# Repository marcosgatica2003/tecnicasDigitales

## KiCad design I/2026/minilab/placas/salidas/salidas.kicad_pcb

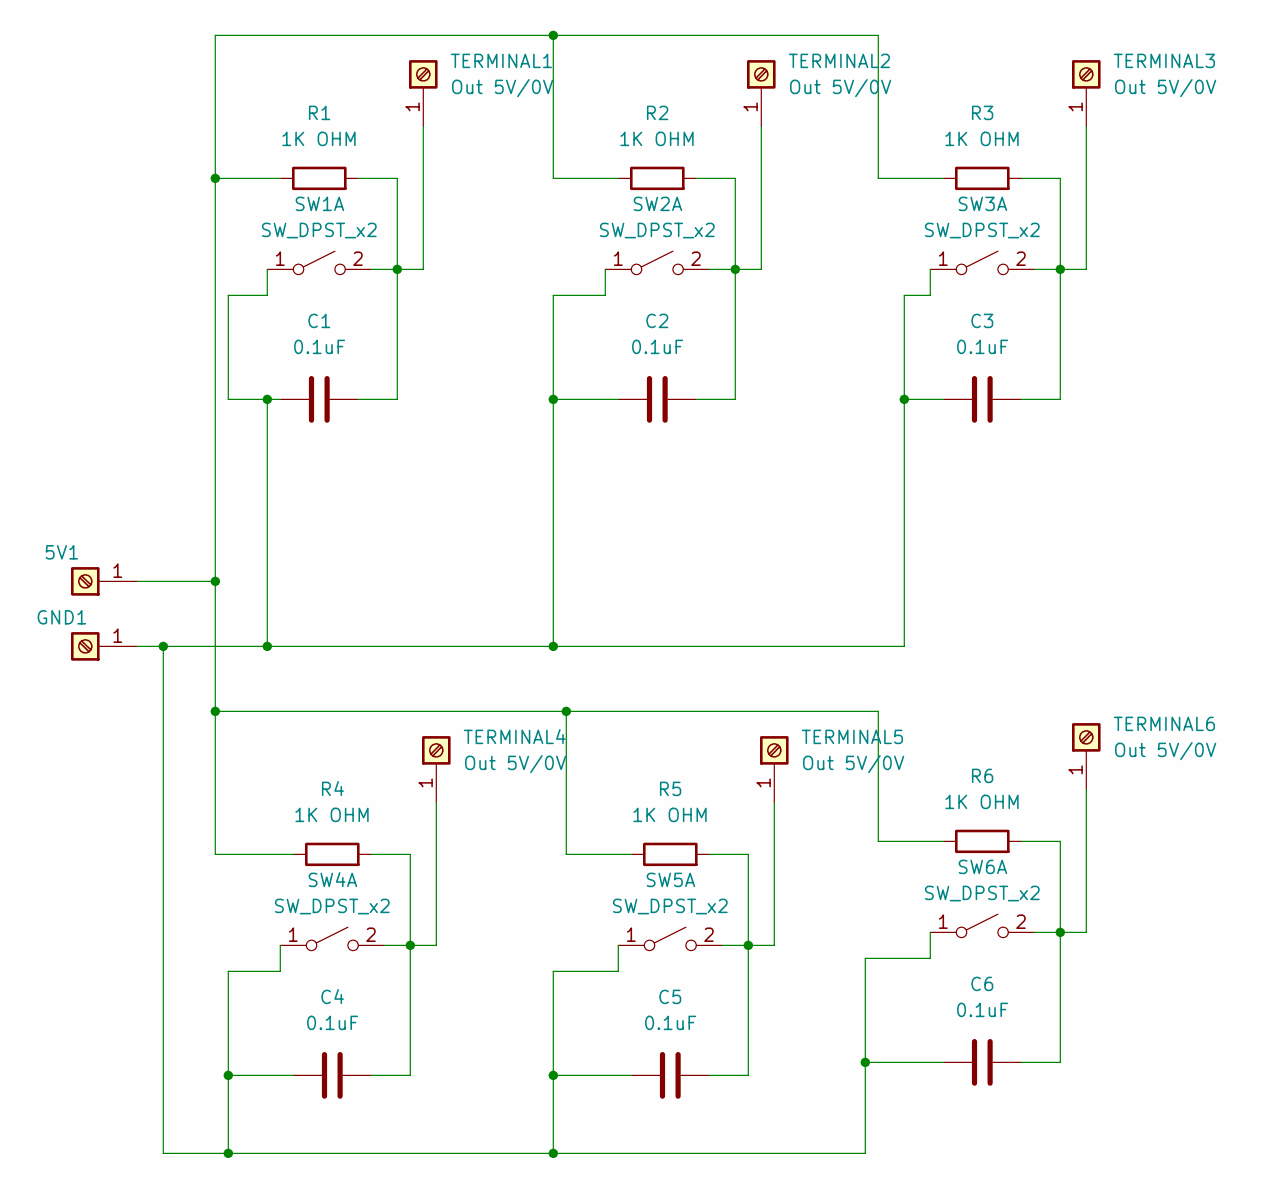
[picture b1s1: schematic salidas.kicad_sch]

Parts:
5V1: PinHeader_1x01_P1.00mm_Vertical
C1, C2, C3, C4, C5, C6: 0.1uF; CP_Radial_D5.0mm_P2.00mm
GND1: PinHeader_1x01_P1.00mm_Vertical
R1, R2, R3, R4, R5, R6: 1K OHM; R_Axial_DIN0207_L6.3mm_D2.5mm_P7.62mm_Horizontal
SW1, SW2, SW3, SW4, SW5, SW6: SW_DPST_x2; SW_DIP_SPSTx01_Slide_9.78x4.72mm_W7.62mm_P2.54mm
TERMINAL1, TERMINAL2, TERMINAL3, TERMINAL4, TERMINAL5, TERMINAL6: Out 5V/0V; PinHeader_1x01_P1.00mm_Vertical

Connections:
unnamed: 5V1.1 (Pin_1_1), R1.1, R2.1, R3.1, R4.1, R5.1, R6.1
unnamed: C1.1, C2.1, C3.1, C4.1, C5.1, C6.1, GND1.1 (Pin_1_1), SW1.1 (A), SW2.1 (A), SW3.1 (A), SW4.1 (A), SW5.1 (A), SW6.1 (A)
unnamed: C1.2, R1.2, SW1.2 (B), TERMINAL1.1 (Pin_1_1)
unnamed: C2.2, R2.2, SW2.2 (B), TERMINAL2.1 (Pin_1_1)
unnamed: C3.2, R3.2, SW3.2 (B), TERMINAL3.1 (Pin_1_1)
unnamed: C4.2, R4.2, SW4.2 (B), TERMINAL4.1 (Pin_1_1)
unnamed: C5.2, R5.2, SW5.2 (B), TERMINAL5.1 (Pin_1_1)
unnamed: C6.2, R6.2, SW6.2 (B), TERMINAL6.1 (Pin_1_1)

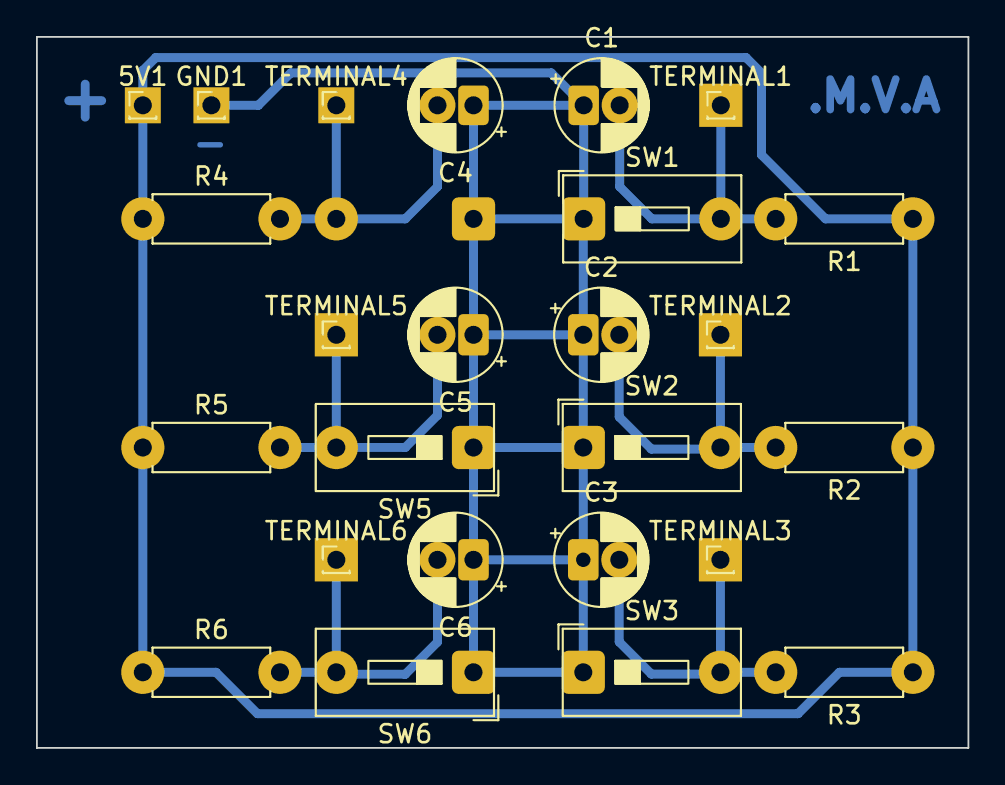
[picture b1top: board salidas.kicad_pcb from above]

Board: 2 copper layers, 51.8 x 39.5 mm, 26 parts (1 on the bottom side), 8 nets.

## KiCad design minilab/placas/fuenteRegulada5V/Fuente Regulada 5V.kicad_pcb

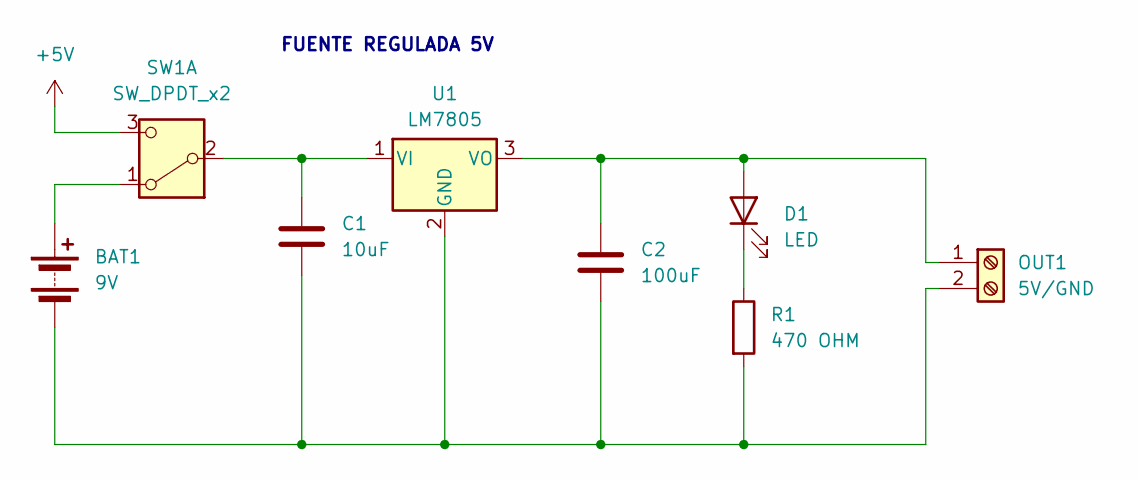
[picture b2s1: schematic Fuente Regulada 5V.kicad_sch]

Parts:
BAT1: 9V; BatteryHolder_MPD_BA9VPC_1xPP3
C1: 10uF; CP_Radial_D4.0mm_P2.00mm
C2: 100uF; C_Radial_D5.0mm_H5.0mm_P2.00mm
D1: LED; LED_D4.0mm
OUT1: 5V/GND; Molex_KK-254_AE-6410-02A_1x02_P2.54mm_Vertical
R1: 470 OHM; R_Axial_DIN0207_L6.3mm_D2.5mm_P7.62mm_Horizontal
SW1: SW_DPDT_x2; SW_Slide_SPDT_Straight_CK_OS102011MS2Q
U1: LM7805; TO-220-3_Vertical

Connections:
+5V: SW1.3 (C)
unnamed: BAT1.1 (+), SW1.1 (A)
unnamed: BAT1.2 (-), C1.2, C2.2, OUT1.2, R1.2, U1.2 (GND)
unnamed: C2.1, D1.2 (A), OUT1.1, U1.3 (VO)
unnamed: D1.1 (K), R1.1
unnamed: C1.1, SW1.2 (B), U1.1 (VI)

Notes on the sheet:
FUENTE REGULADA 5V

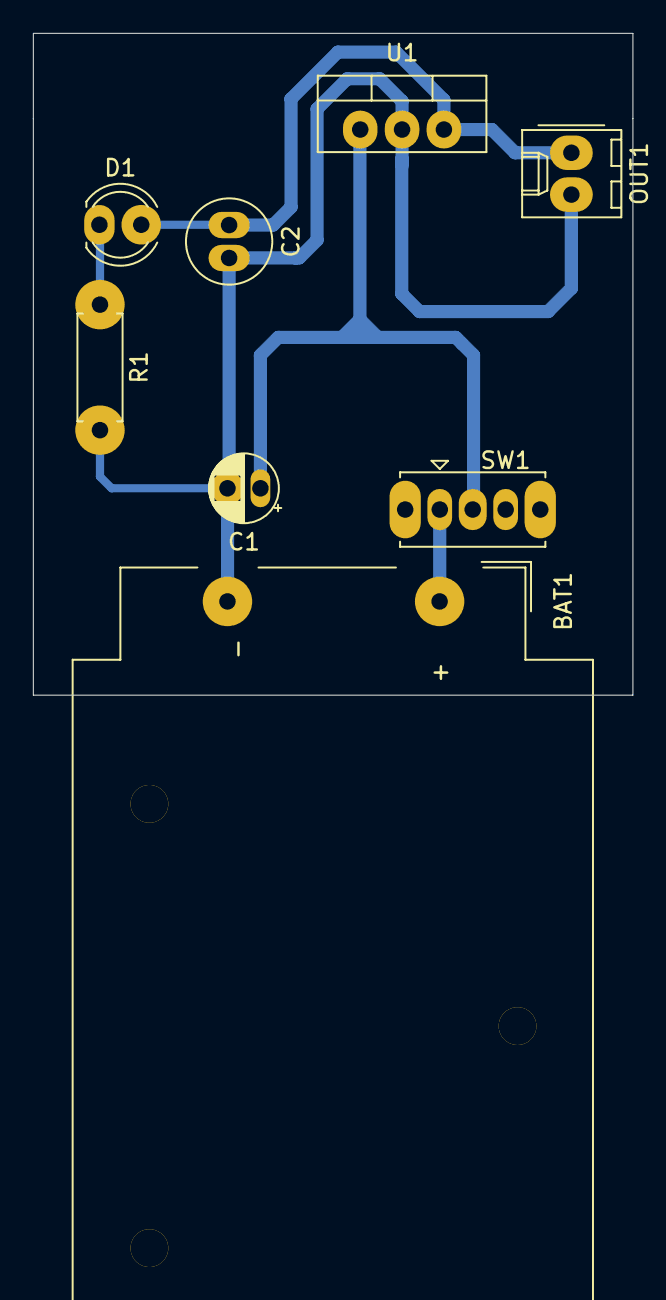
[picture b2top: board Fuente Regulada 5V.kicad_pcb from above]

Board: 2 copper layers, 36.4 x 40.2 mm, 8 parts (0 on the bottom side), 5 nets.

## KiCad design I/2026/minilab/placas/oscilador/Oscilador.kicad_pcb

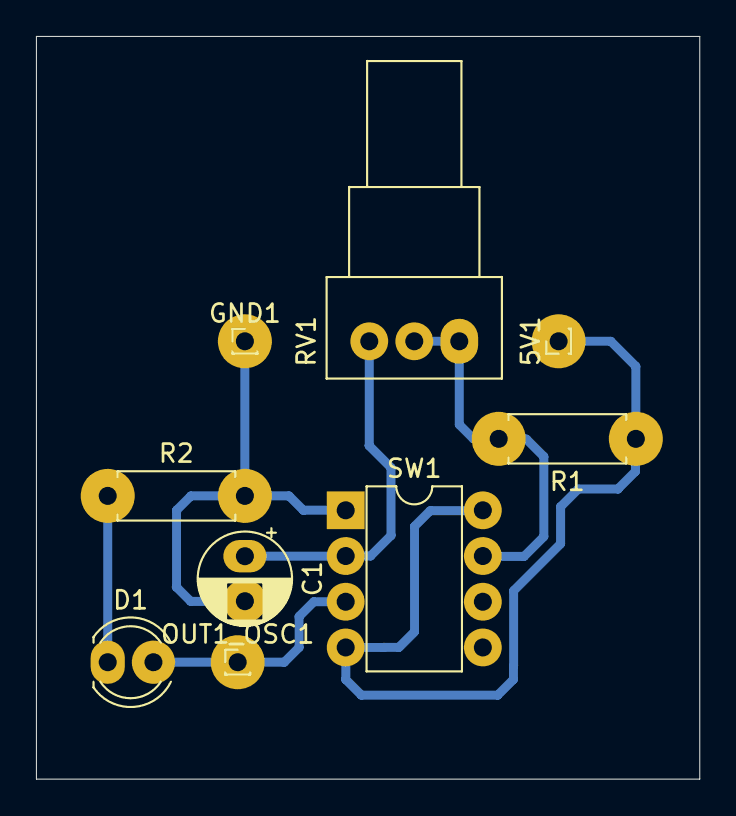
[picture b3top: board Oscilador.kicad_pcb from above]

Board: 2 copper layers, 36.8 x 41.3 mm, 9 parts (0 on the bottom side), 6 nets.

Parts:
5V1: PinHeader_1x01_P1.00mm_Vertical
C1: 0.47uF; CP_Radial_D5.0mm_P2.50mm
D1: LED; LED_D4.0mm
GND1: PinHeader_1x01_P1.00mm_Vertical
OUT1_OSC1: PinHeader_1x01_P1.00mm_Vertical
R1: 2.7k OHM; R_Axial_DIN0207_L6.3mm_D2.5mm_P7.62mm_Horizontal
R2: 470 OHM; R_Axial_DIN0207_L6.3mm_D2.5mm_P7.62mm_Horizontal
RV1: 1M OHM; Potentiometer_Alps_RK09Y11_Single_Horizontal
SW1: SW_DIP_x04; DIP-8_W7.62mm

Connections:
unnamed: 5V1.1, R1.1, SW1.4, SW1.8
unnamed: C1.1, RV1.3, SW1.2
unnamed: D1.2 (A), OUT1_OSC1.1, SW1.3
unnamed: D1.1 (K), R2.1
unnamed: C1.2, GND1.1, R2.2, SW1.1
unnamed: R1.2, RV1.1, RV1.2, SW1.7

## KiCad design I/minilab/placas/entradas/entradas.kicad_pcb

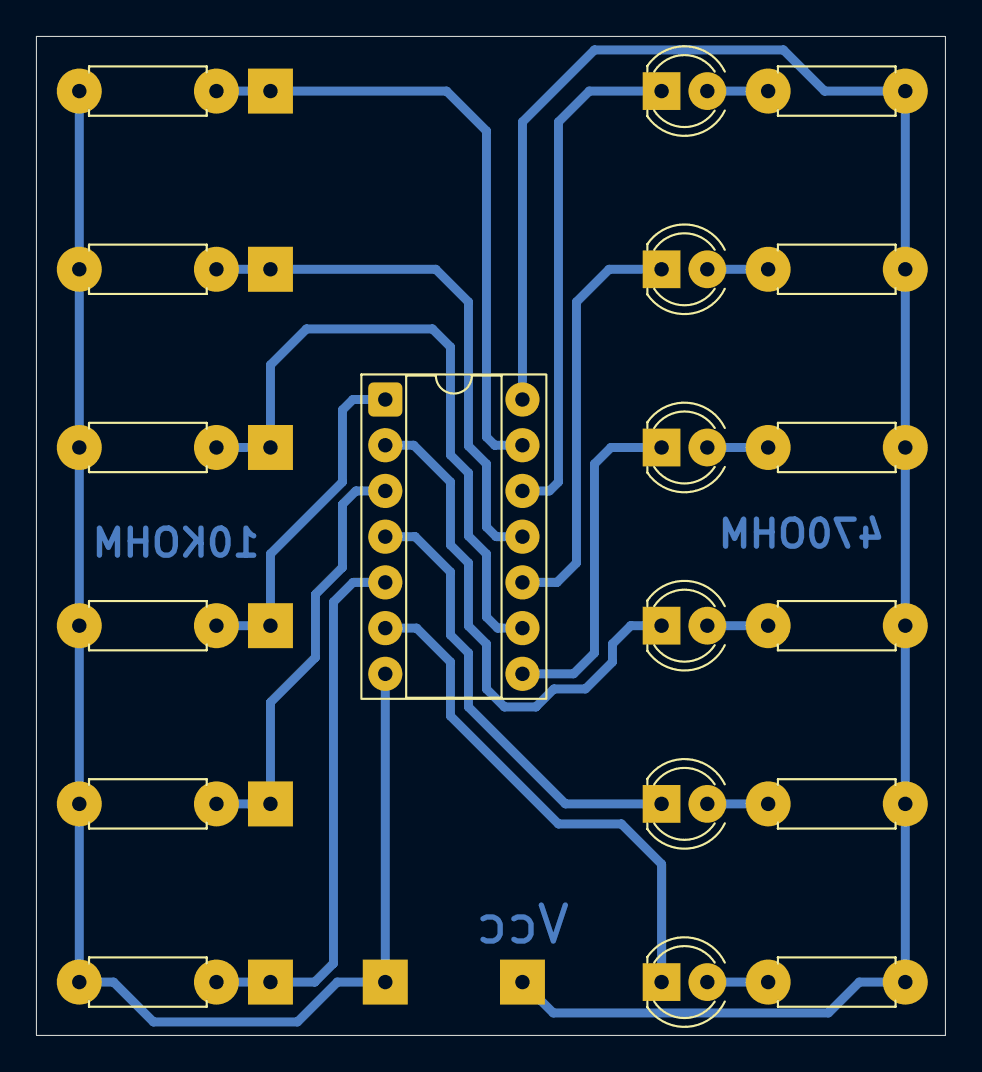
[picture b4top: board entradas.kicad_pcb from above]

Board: 2 copper layers, 50.5 x 55.5 mm, 27 parts (0 on the bottom side), 20 nets.

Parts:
5V1: PinHeader_1x01_P1.00mm_VerticalBIG
D1, D2, D3, D4, D5, D6: LED; LED_D4.0mmBIG
GND1: PinHeader_1x01_P1.00mm_VerticalBIG
INPUT1, INPUT2, INPUT3, INPUT4, INPUT5, INPUT6: PinHeader_1x01_P1.00mm_VerticalBIG
R7, R9, R11, R13, R15, R17: 470 OHM; R_Axial_DIN0207_L6.3mm_D2.5mm_P7.62mm_HorizontalBIG
R8, R10, R12, R14, R16, R18: 10 OHM; R_Axial_DIN0207_L6.3mm_D2.5mm_P7.62mm_HorizontalBIG
SW7: SW_DIP_x07; DIP-14_W7.62mm_SocketBIG

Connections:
unnamed: 5V1.1, R7.1, R9.1, R11.1, R13.1, R15.1, R17.1, SW7.14
unnamed: D1.2 (A), R7.2
unnamed: D1.1 (K), SW7.12
unnamed: D2.2 (A), R9.2
unnamed: D2.1 (K), SW7.10
unnamed: D3.2 (A), R11.2
unnamed: D3.1 (K), SW7.8
unnamed: D4.2 (A), R13.2
unnamed: D4.1 (K), SW7.2
unnamed: D5.2 (A), R15.2
unnamed: D5.1 (K), SW7.4
unnamed: D6.2 (A), R17.2
unnamed: D6.1 (K), SW7.6
unnamed: GND1.1, R8.2, R10.2, R12.2, R14.2, R16.2, R18.2, SW7.7
unnamed: INPUT1.1, R8.1, SW7.13
unnamed: INPUT2.1, R10.1, SW7.11
unnamed: INPUT3.1, R12.1, SW7.9
unnamed: INPUT4.1, R14.1, SW7.1
unnamed: INPUT5.1, R16.1, SW7.3
unnamed: INPUT6.1, R18.1, SW7.5

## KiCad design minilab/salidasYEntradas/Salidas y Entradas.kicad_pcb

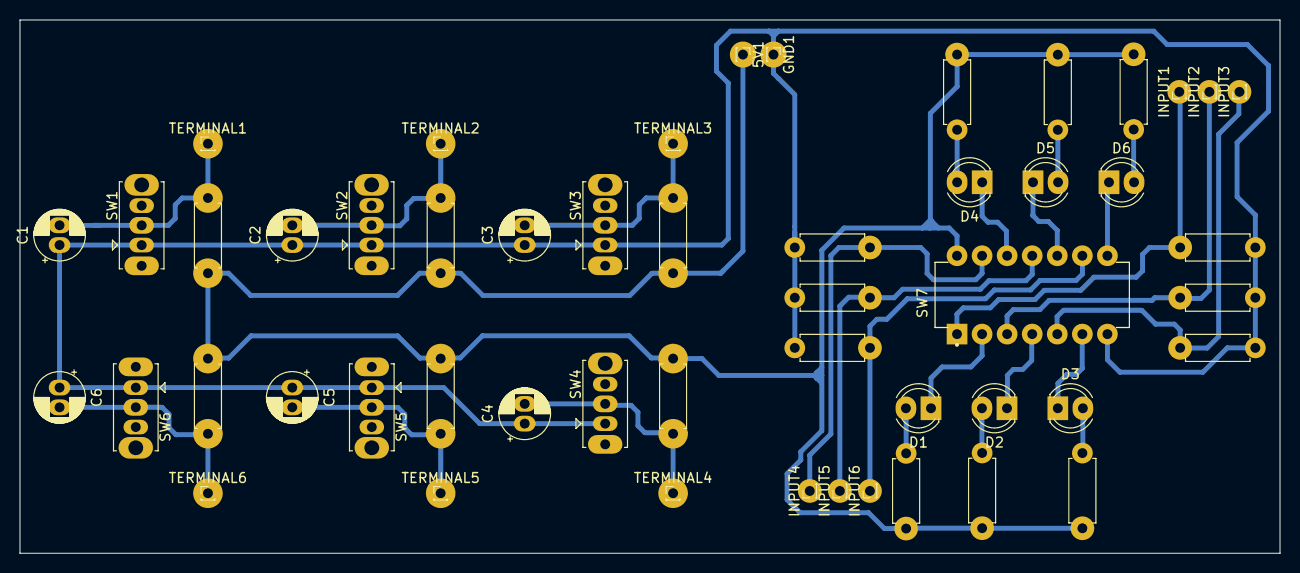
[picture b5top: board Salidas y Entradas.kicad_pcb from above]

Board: 2 copper layers, 127.7 x 54.0 mm, 51 parts (0 on the bottom side), 26 nets.

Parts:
5V1: PinHeader_1x01_P1.00mm_VerticalPAD2.5mm
C1, C2, C3, C4, C5, C6: 0.1uF; CP_Radial_D5.0mm_P2.00mmPAD2.2mm
D1, D2, D3, D4, D5, D6: LED; LED_D4.0mmPAD2,4mm
GND1: PinHeader_1x01_P1.00mm_VerticalPAD2.5mm
INPUT1, INPUT2, INPUT3, INPUT4, INPUT5, INPUT6: PinHeader_1x01_P1.00mm_VerticalPAD2.5mm
R1, R2, R3, R4, R5, R6: 1K OHM; R_Axial_DIN0207_L6.3mm_D2.5mm_P7.62mm_HorizontalPAD2.5mm
R7, R9, R11, R13, R15, R17: 470 OHM; R_Axial_DIN0207_L6.3mm_D2.5mm_P7.62mm_HorizontalPAD2.5mm
R8, R10, R12, R14, R16, R18: 10 OHM; R_Axial_DIN0207_L6.3mm_D2.5mm_P7.62mm_HorizontalPAD2.5mm
SW1, SW2, SW3, SW4, SW5, SW6: SW_DPDT_x2; SW_Slide_SPDT_Straight_CK_OS102011MS2QPADGRANDE
SW7: SW_DIP_x07; DIP794W45P254L1969H508Q14PAD2.1mm
TERMINAL1, TERMINAL2, TERMINAL3, TERMINAL4, TERMINAL5, TERMINAL6: Out 5V/0V; PinHeader_1x01_P1.00mm_VerticalPAD2.5mm

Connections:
unnamed: 5V1.1, R1.1, R2.1, R3.1, R4.1, R5.1, R6.1, R7.1, R9.1, R11.1, R13.1, R15.1, R17.1, SW7.14
unnamed: D1.2 (A), R7.2
unnamed: D1.1 (K), SW7.2
unnamed: D2.2 (A), R9.2
unnamed: D2.1 (K), SW7.4
unnamed: D3.2 (A), R11.2
unnamed: D3.1 (K), SW7.6
unnamed: D4.2 (A), R13.2
unnamed: D4.1 (K), SW7.12
unnamed: D5.2 (A), R15.2
unnamed: D5.1 (K), SW7.10
unnamed: D6.2 (A), R17.2
unnamed: D6.1 (K), SW7.8
unnamed: C1.1, C2.1, C3.1, C4.1, C5.1, C6.1, GND1.1, R8.2, R10.2, R12.2, R14.2, R16.2, R18.2, SW1.1 (A), SW2.1 (A), SW3.1 (A), SW4.1 (A), SW5.1 (A), SW6.1 (A), SW7.7
unnamed: INPUT1.1, R8.1, SW7.1
unnamed: INPUT2.1, R10.1, SW7.3
unnamed: INPUT3.1, R12.1, SW7.5
unnamed: INPUT4.1, R14.1, SW7.13
unnamed: INPUT5.1, R16.1, SW7.11
unnamed: INPUT6.1, R18.1, SW7.9
unnamed: C1.2, R1.2, SW1.2 (B), TERMINAL1.1
unnamed: C2.2, R2.2, SW2.2 (B), TERMINAL2.1
unnamed: C3.2, R3.2, SW3.2 (B), TERMINAL3.1
unnamed: C4.2, R4.2, SW4.2 (B), TERMINAL4.1
unnamed: C5.2, R5.2, SW5.2 (B), TERMINAL5.1
unnamed: C6.2, R6.2, SW6.2 (B), TERMINAL6.1

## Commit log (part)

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2024-10-31 Reescriptura de directorios
2025-03-27 Creado directorio minilab - mv fuente, oscilador y s.e. ahí
2025-03-27 Agregado de los apuntes del práctico
2025-04-25 Correciones del minilab & listo para imprimir
2025-05-13 Vivado ejercicios
2025-05-13 Agregado de filminas del teorico
2025-05-16 pptx, ppt -> pdf
2025-05-25 Agregado de plantilla para informes en minilab
2025-05-25 Reorganización del directorio minilab
2025-06-04 Actualización de cosas del minilab kicad
2025-06-04 Agregado de parciales
2025-06-13 Agregado de bibliotecas de simbolos
2025-06-13 Separado de placa de entradas y salidas
2025-06-13 Agregado de consigna de minilab
2025-06-13 Añadido de Placas para imprimir
2025-06-13 Correción de archivos de impresión
2025-06-15 Agregado de archivos de la comunidad
2025-06-15 Progreso informe lab 1
2025-06-15 Agregado de gitignore
2025-06-17 Agregado de 'lck' a gitignore
2025-06-18 Progreso informe tp1
2025-06-18 Agregado de inicio y final código en tp1
2025-06-18 Informe tp1 90% hecho
2025-06-21 Agregado de directorio 'trabajosPracticos' y movido el p.l.1
2025-06-24 Informe p.l.1 terminado
2025-06-24 Agregado de libros
2025-09-24 Terminado informe tp2
2025-10-02 Borrado de bibliotecaDeSimbolos (posiblemente rao metió esto)
2025-11-27 Tp3 terminado
2026-04-01 Agregado de clases 16 al 29
2026-04-01 Agregado de información del cursado
2026-04-01 Organización
2026-04-02 Agregado de 2026
2026-04-04 Cambio de nombre
2026-04-16 Agregado de cosas útiles
2026-04-16 Agregado de chasis en freecad
2026-04-16 Progreso tarea 001
2026-04-16 Simulación
2026-04-17 Finalizado tarea 001
2026-04-17 Achicado de base para dar grosor de 3mm
2026-04-18 Progreso con segunda pieza
2026-04-30 Agregado de informe (parte del causa)
2026-05-05 Agregados de datos del informe
2026-05-05 Informe tp0
2026-05-05 Comienzo actividad 2-1
2026-05-07 Progreso
2026-05-08 Avances
2026-05-14 Agregado de falstad archivos
2026-05-14 Progreso 70%
2026-05-14 Informe 0-elMiniLab terminado
2026-05-14 Informe terminado 0-elMiniLab (archivos tex y pdf)
2026-05-14 Agregado del 8
2026-05-14 Informe terminado
2026-05-14 Agregado de los ejercicios en xilinx
2026-05-15 Agregado de .zip
2026-05-22 Agregado de material teorico
2026-05-22 Comienzo de tp2
2026-05-22 Agregado de unidad 2
2026-05-22 Agregado de unidad 3
2026-05-22 Agregado de unidad4
2026-05-22 Agregado de unidad 1 en el práctico
2026-05-23 Agregado de respuestas de tarea 3
2026-06-10 Agregado de informe random para comenzar el tp1
2026-06-10 Agregado de clase 5
2026-06-20 Continuación tp1
2026-06-20 Agregado de archivos de tables generator
2026-06-21 Continuación del 2.2
2026-06-21 Continuación de 2.2
2026-06-22 PUNTO 2 casi listo
2026-06-22 Agregado de circuito 2.1 falstad
2026-06-25 TP1 terminado
2026-06-28 Tarea de Hamming terminada
